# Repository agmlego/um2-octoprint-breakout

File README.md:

This is a breakout for octoprint, compatible with the Ender3S1 display.

### Pinout
| J1 Pin | GPIO Pin | Mux      | Purpose                 |
|--------|----------|----------|-------------------------|
| 3      | 2        |          | N/C                     |
| 5      | 3        | `GPIO3`  | Power button            |
| 7      | 4        | `TXD3`   | Display, `UART3`        |
| 8      | 14       | `TXD0`   | Printer, `UART0`        |
| 10     | 15       | `RXD0`   | Printer, `UART0`        |
| 11     | 17       | `GPIO17` | Power button blue LED   |
| 12     | 18       | `PWM0`   | Pi cooling fan PWM      |
| 13     | 27       | `GPIO27` | Power button red LED    |
| 15     | 22       | `GPIO22` | Printer power-on detect |
| 16     | 23       | `GPIO23` | Printer power relay     |
| 18     | 24       | `GPIO24` | Power button green LED  |
| 19     | 10       | `SDA5`   | I2C header, `I2C5`      |
| 21     | 9        |          | N/C                     |
| 22     | 25       |          | N/C                     |
| 23     | 11       | `SCL5`   | I2C header, `I2C5`      |
| 24     | 8        |          | N/C                     |
| 26     | 7        |          | N/C                     |
| 27     | 0        | `ID_SD`  | HAT+ EEPROM, `I2C0`     |
| 28     | 1        | `ID_SC`  | HAT+ EEPROM, `I2C0`     |
| 29     | 5        | `RXD3`   | Display, `UART3`        |
| 31     | 6        |          | N/C                     |
| 32     | 12       | `GPIO12` | Encoder click           |
| 33     | 13       | `GPIO13` | Display beeper          |
| 35     | 19       | `GPIO19` | Encoder channel B       |
| 36     | 16       |          | N/C                     |
| 37     | 26       | `GPIO26` | Encoder channel A       |
| 38     | 20       |          | N/C                     |
| 40     | 21       |          | N/C                     |

### Images
[Interactive BOM](bom/ibom.html)

### Device Tree Overlay
```
# Power button
dtoverlay=gpio-shutdown
# Automated blower control
dtoverlay=pwm-gpio-fan,fan_gpio=18
# Printer power
gpio=23=op,dl
# LEDs
dtoverlay=gpio-led,gpio=17,label=blue,trigger=actpwr
dtoverlay=gpio-led,gpio=24,label=green
dtoverlay=gpio-led,gpio=27,label=red
# Display controls
dtoverlay=gpio-key,gpio=12,label=knobpress,keycode=256
dtoverlay=rotary-encoder,pin_a=19,pin_b=26,relative_axis=1
# Display UART
dtoverlay=uart3
# Beeper
gpio=13=op,dl
# Power sense
gpio=22=ip,np
# I2C
dtoverlay=i2c5,pins_10_11=1,baudrate=400000
```

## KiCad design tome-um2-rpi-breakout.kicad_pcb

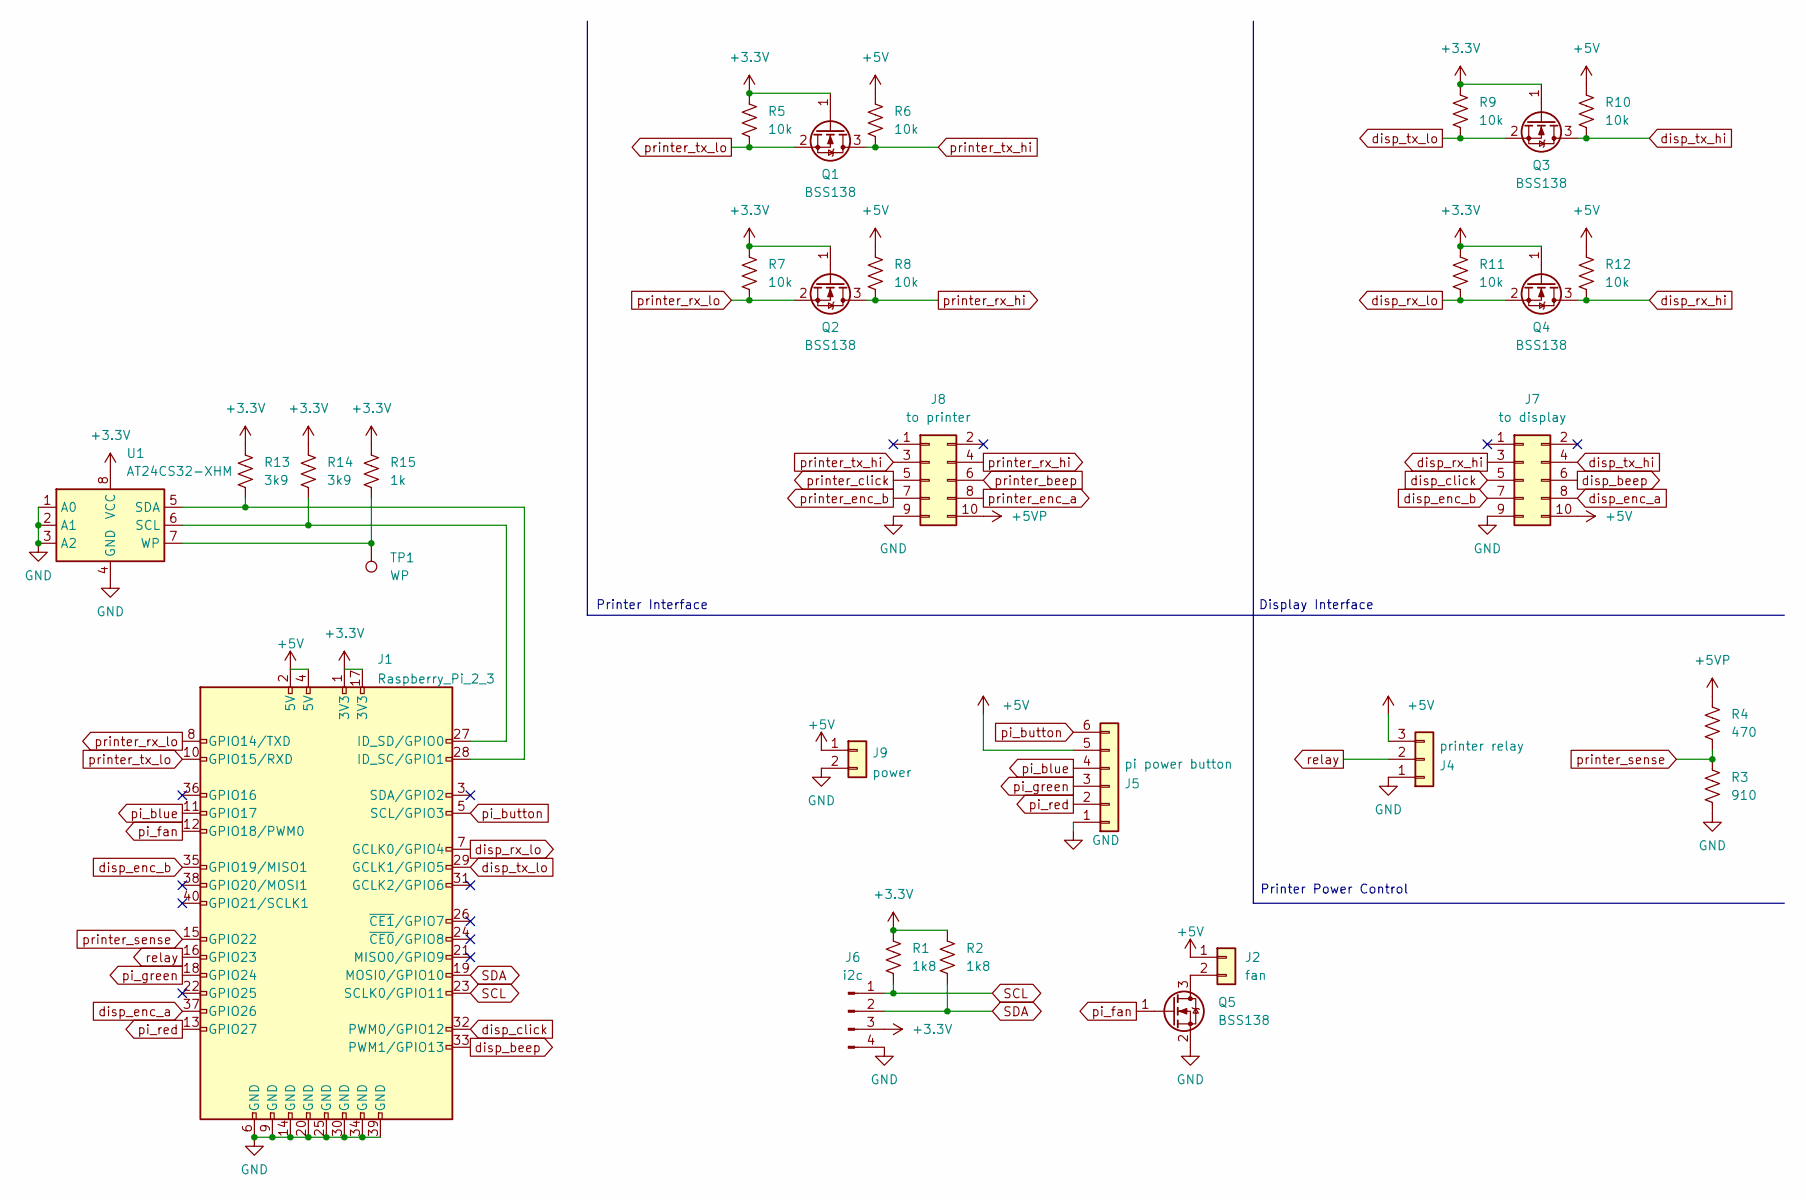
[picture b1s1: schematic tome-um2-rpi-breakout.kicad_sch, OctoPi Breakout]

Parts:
J1: Raspberry_Pi_2_3; RPI_Hat_B+
J2: fan; JST_XH_S2B-XH-A_1x02_P2.50mm_Horizontal
J4: printer relay; JST_XH_S3B-XH-A_1x03_P2.50mm_Horizontal
J5: pi power button; JST_XH_S6B-XH-A_1x06_P2.50mm_Horizontal
J6: i2c; JST_XH_S4B-XH-A-1_1x04_P2.50mm_Horizontal
J7: to display; IDC-Header_2x05_P2.54mm_Horizontal
J8: to printer; IDC-Header_2x05_P2.54mm_Horizontal
J9: power; JST_XH_S2B-XH-A_1x02_P2.50mm_Horizontal
Q1, Q2, Q3, Q4, Q5: BSS138; SOT-23
R1, R2: 1k8; R_0805_2012Metric_Pad1.20x1.40mm_HandSolder
R3: 910; R_0805_2012Metric_Pad1.20x1.40mm_HandSolder
R4: 470; R_0805_2012Metric_Pad1.20x1.40mm_HandSolder
R5, R6, R7, R8, R9, R10, R11, R12: 10k; R_0805_2012Metric_Pad1.20x1.40mm_HandSolder
R13, R14: 3k9; R_0805_2012Metric_Pad1.20x1.40mm_HandSolder
R15: 1k; R_0805_2012Metric_Pad1.20x1.40mm_HandSolder
TP1: WP; TestPoint_Keystone_5010-5014_Multipurpose
U1: AT24CS32-XHM; TSSOP-8_4.4x3mm_P0.65mm

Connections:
+3.3V: J1.1 (3V3), J1.17 (3V3), J6.3, Q1.1 (G), Q2.1 (G), Q3.1 (G), Q4.1 (G), R1.1, R2.1, R5.1, R7.1, R9.1, R11.1, R13.1, R14.1, R15.1, U1.8 (VCC)
+5V: J1.2 (5V), J1.4 (5V), J2.1, J4.3, J5.5, J7.10, J9.1, R6.1, R8.1, R10.1, R12.1
+5VP: J8.10, R4.1
GND: J1.6 (GND), J1.9 (GND), J1.14 (GND), J1.20 (GND), J1.25 (GND), J1.30 (GND), J1.34 (GND), J1.39 (GND), J4.1, J5.1, J6.4, J7.9, J8.9, J9.2, Q5.2 (S), R3.2, U1.1 (A0), U1.2 (A1), U1.3 (A2), U1.4 (GND)
unnamed: J1.28 (ID_SC/GPIO1), R13.2, U1.5 (SDA)
unnamed: J1.27 (ID_SD/GPIO0), R14.2, U1.6 (SCL)
unnamed: J2.2, Q5.3 (D)
unnamed: R15.2, TP1.1, U1.7 (WP)
SCL: J1.23 (SCLK0/GPIO11), J6.1, R1.2
SDA: J1.19 (MOSI0/GPIO10), J6.2, R2.2
disp_beep: J1.33 (PWM1/GPIO13), J7.6
disp_click: J1.32 (PWM0/GPIO12), J7.5
disp_enc_a: J1.37 (GPIO26), J7.8
disp_enc_b: J1.35 (GPIO19/MISO1), J7.7
disp_rx_hi: J7.3, Q4.3 (D), R12.2
disp_rx_lo: J1.7 (GCLK0/GPIO4), Q4.2 (S), R11.2
disp_tx_hi: J7.4, Q3.3 (D), R10.2
disp_tx_lo: J1.29 (GCLK1/GPIO5), Q3.2 (S), R9.2
pi_blue: J1.11 (GPIO17), J5.4
pi_button: J1.5 (SCL/GPIO3), J5.6
pi_fan: J1.12 (GPIO18/PWM0), Q5.1 (G)
pi_green: J1.18 (GPIO24), J5.3
pi_red: J1.13 (GPIO27), J5.2
printer_beep: J8.6
printer_click: J8.5
printer_enc_a: J8.8
printer_enc_b: J8.7
printer_rx_hi: J8.4, Q2.3 (D), R8.2
printer_rx_lo: J1.8 (GPIO14/TXD), Q2.2 (S), R7.2
printer_sense: J1.15 (GPIO22), R3.1, R4.2
printer_tx_hi: J8.3, Q1.3 (D), R6.2
printer_tx_lo: J1.10 (GPIO15/RXD), Q1.2 (S), R5.2
relay: J1.16 (GPIO23), J4.2

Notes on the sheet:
Printer Interface
Display Interface
Printer Power Control

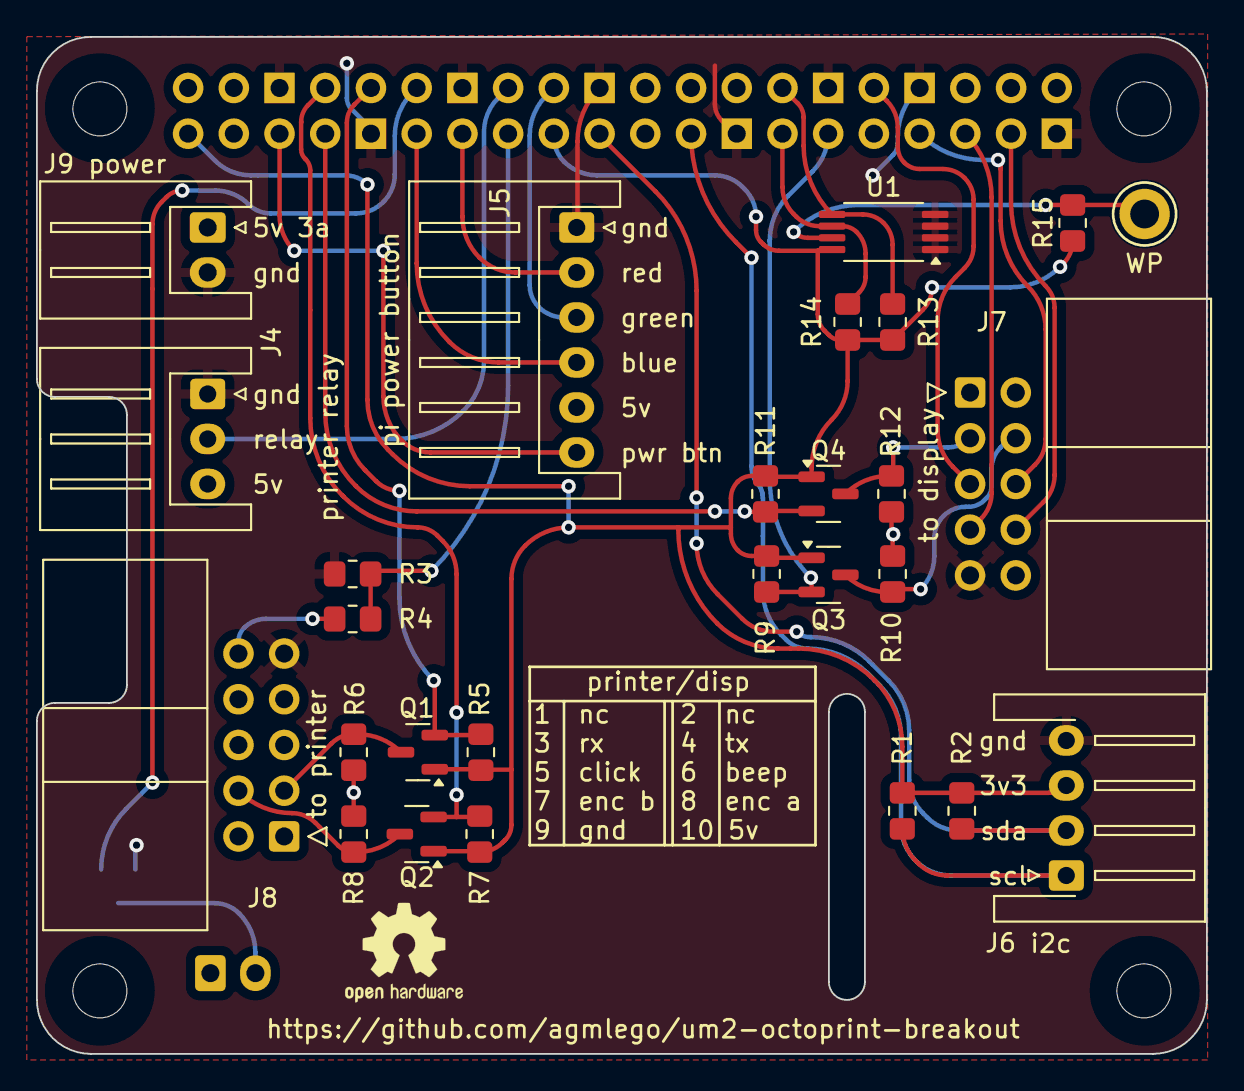
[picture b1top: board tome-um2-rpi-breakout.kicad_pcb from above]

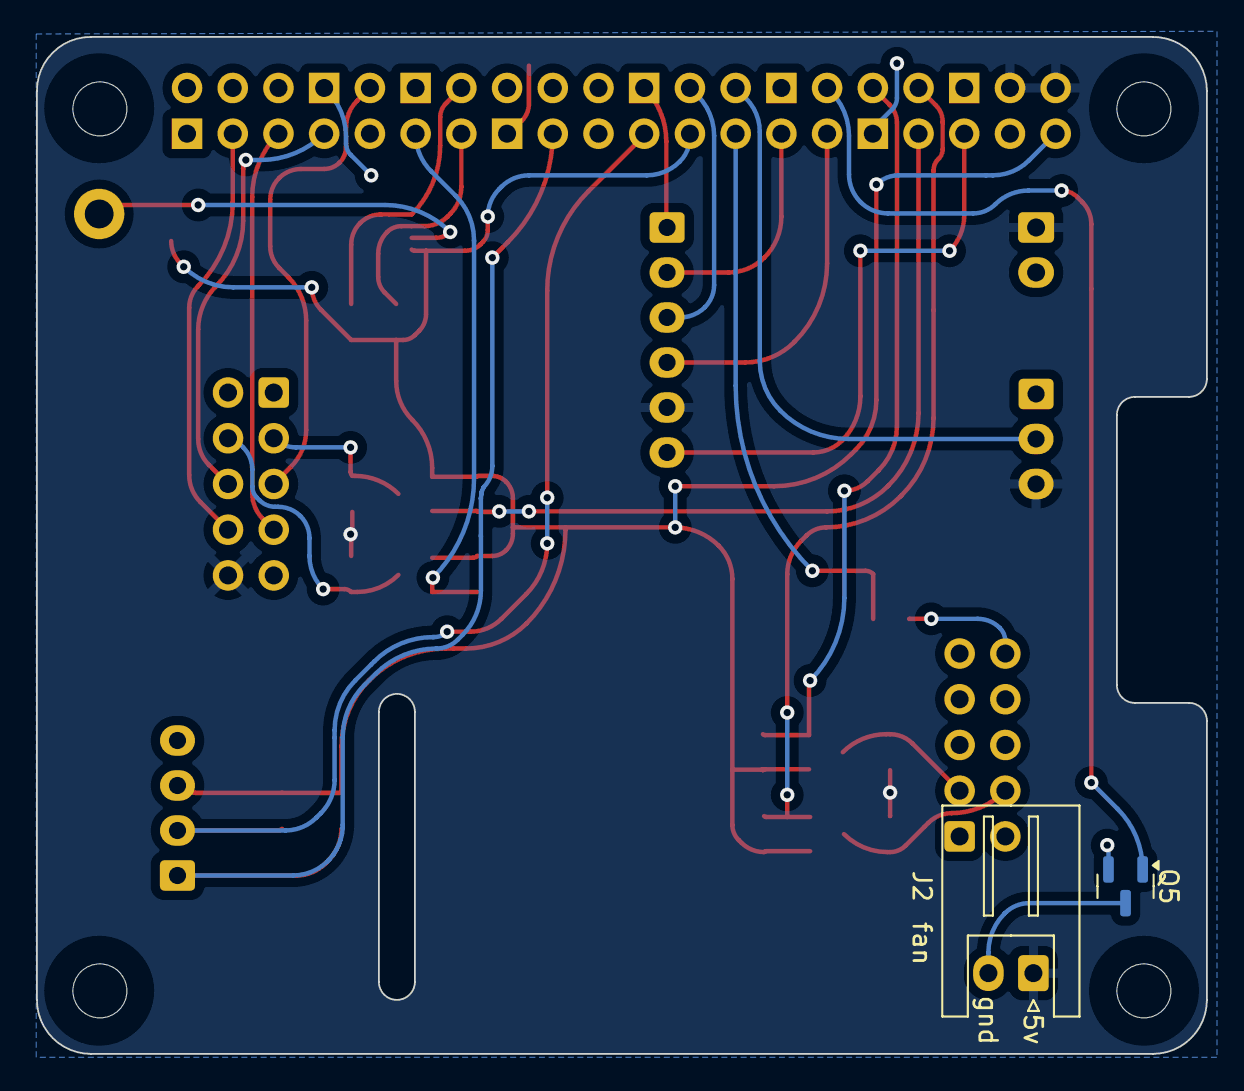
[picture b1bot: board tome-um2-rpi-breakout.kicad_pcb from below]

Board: 2 copper layers, 65.0 x 56.5 mm, 30 parts (2 on the bottom side), 29 nets.

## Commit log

2022-03-14 README.md
2024-12-02 Refactored to meet the HAT+ specification and MITM the Ender 3S1 display bus.
2024-12-02 Assigned footprints
2024-12-03 Added RPi HAT submodule
2024-12-03 Changed footprints to 0805
2024-12-03 Swap encoder pins for routing
2024-12-03 Swap display click and beep for routing
2024-12-03 Swap red and blue for routing
2024-12-03 Actually connect grounds...
2024-12-03 Move external i2c port to i2c5 for routing
2024-12-03 Finished routing
2024-12-03 Labeling, pin swaps for `gpio-fan` and `gpio-key`
2024-12-03 Labeling changes
2024-12-03 ibom generation
2024-12-03 Swapped `pi_fan` and `pi_green` for compatibility with `gpio-fan` using `PWM0`
2024-12-03 Add PCB and ibom render actions
2024-12-03 Add links to PCB images and ibom
2024-12-03 Removed manually-generated ibom
2024-12-03 Try single item in blacklist
2024-12-03 Switched back to manually-generated ibom because the render pipeline chokes on a footprint (probably the RPI HAT one)
2025-01-20 Generated STEP file of board for case design
2025-01-20 Added Device Tree overlay section
